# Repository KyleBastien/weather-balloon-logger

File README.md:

# Weather Balloon Logger LightHAB carrier

This repository contains a hand-solderable through-hole carrier for the QRP Labs LightHABTracker 1.0 and SparkFun OpenLog. LightHAB's exposed 3.3 V rail powers the logger directly.

| Directory | Contents |
| --- | --- |
| `docs/` | Electrical, mechanical, BOM, purchasing, and release records |
| `library/` | Project KiCad symbols and through-hole footprints |
| `firmware/` | LightHAB upstream integration scaffold and test plan |
| `outputs/` | Review renders, fit sheet, BOM, Gerbers, drill, DXF, and STEP |
| `scripts/` | Deterministic board rebuild, export, and audit tools |

## Project release status

This repository now contains the Weather Balloon Logger carrier design and its
review exports. It is **not yet released for fabrication** because the purchased LightHAB must be measured before its connector and mounting geometry can be finalized. See
[`docs/FABRICATION_READINESS.md`](docs/FABRICATION_READINESS.md) for the exact
engineering-prototype and flight-candidate gates.

## Working locally

The CLI needs no account and no cloud:

```bash
npm i -g copperhead
copperhead check          # ERC, DRC, and doc drift. No model, no network.
copperhead do "..."       # propose, edit, verify, commit
```

The current PCB has zero SMD pads, zero unconnected items, and a prominent no-fabrication warning in the provisional module area.

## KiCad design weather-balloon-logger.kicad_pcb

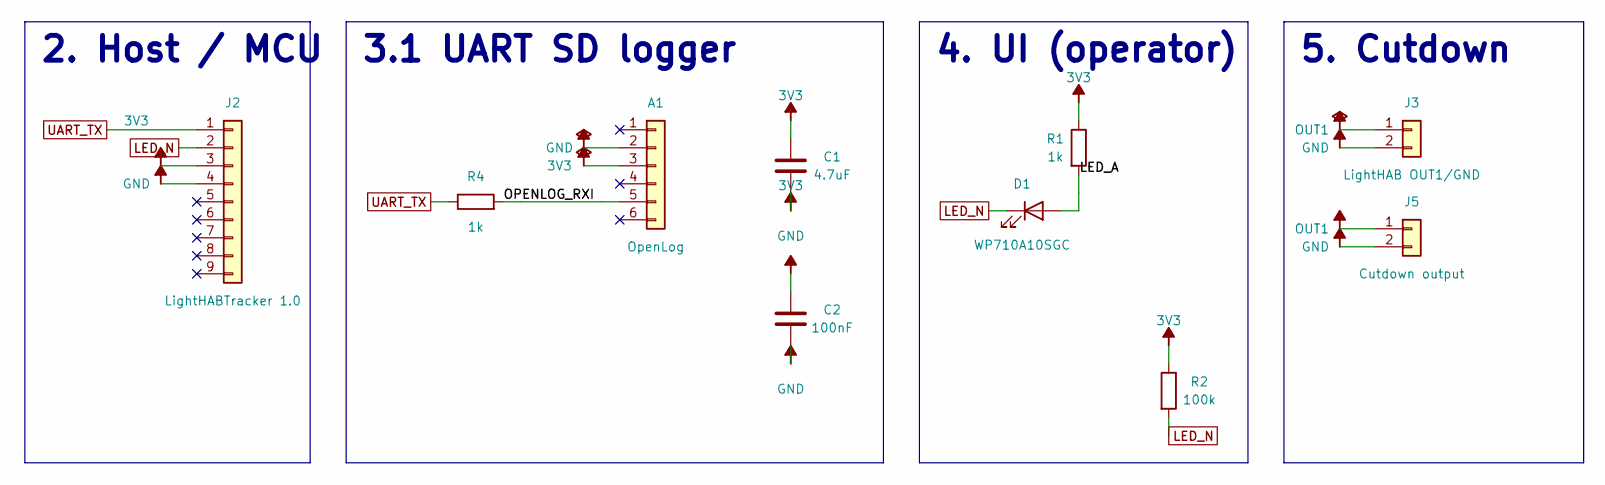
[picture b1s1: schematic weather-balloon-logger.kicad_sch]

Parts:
A1: OpenLog; SparkFun_OpenLog_DEV-13712_Carrier; MPN DEV-13955
C1: 4.7uF; KEMET_C322C475K5R5TA; MPN C322C475K5R5TA
C2: 100nF; KEMET_C315C104K5R5TA; MPN C315C104K5R5TA
D1: WP710A10SGC; LED_D3.0mm; MPN WP710A10SGC
J2: LightHABTracker 1.0; PinHeader_1x09_P2.54mm_Vertical; MPN TBD-LightHAB-1x9
J3: LightHAB OUT1/GND; PinHeader_1x02_P2.54mm_Vertical; MPN TBD-LightHAB-OUT1
J5: Cutdown output; JST_XH_S2B-XH-A_1x02_P2.50mm_Horizontal; MPN S2B-XH-A(LF)(SN)
R1, R4: 1k; R_Axial_DIN0207_L6.3mm_D2.5mm_P7.62mm_Horizontal; MPN MFR-25FBF52-1K
R2: 100k; R_Axial_DIN0207_L6.3mm_D2.5mm_P7.62mm_Horizontal; MPN MFR-25FBF52-100K

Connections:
3V3: A1.3, C1.1, C2.1, J2.3, R1.1, R2.1
GND: A1.2, C1.2, C2.2, J2.4, J3.2, J5.2
LED_A: D1.2 (A), R1.2
LED_N: D1.1 (K), J2.2, R2.2
OPENLOG_RXI: A1.5, R4.2
OUT1: J3.1, J5.1
UART_TX: J2.1, R4.1

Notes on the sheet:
2. Host / MCU
3.1 UART SD logger
4. UI (operator)
5. Cutdown

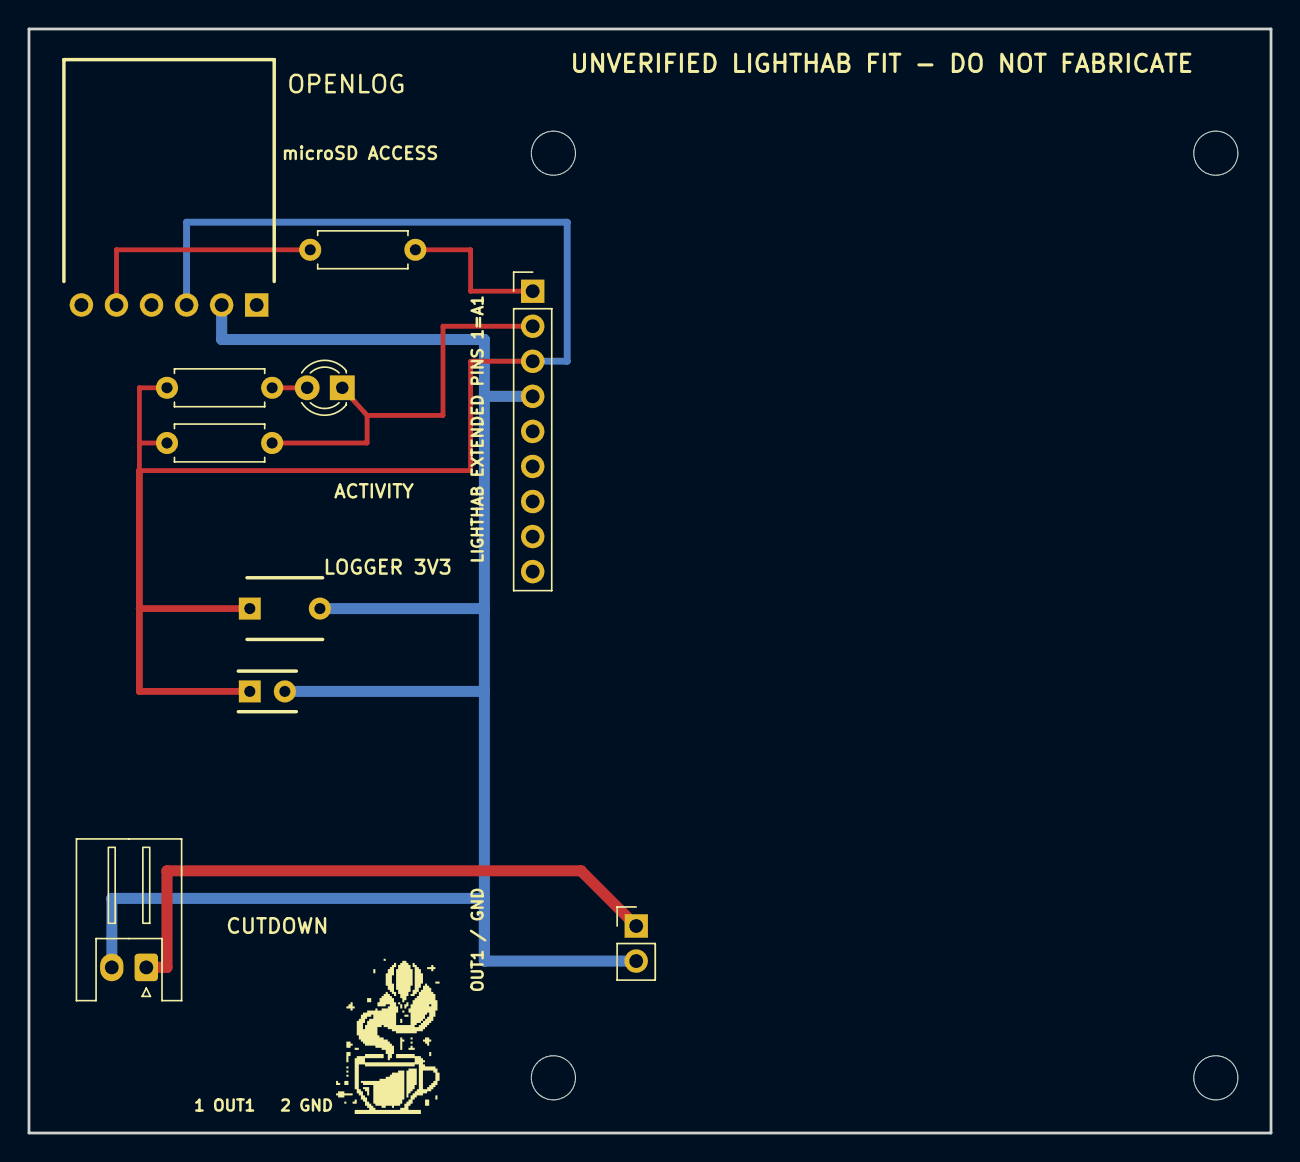
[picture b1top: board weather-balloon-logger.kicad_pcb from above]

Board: 2 copper layers, 90.0 x 80.0 mm, 15 parts (0 on the bottom side), 7 nets.

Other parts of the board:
G1: Coffee Balloon; CoffeeBalloon_7.5x11.25mm
H1, H2, H3, H4: LIGHTHAB HOLE - UNVERIFIED; MountingHole_3.2mm_M3
